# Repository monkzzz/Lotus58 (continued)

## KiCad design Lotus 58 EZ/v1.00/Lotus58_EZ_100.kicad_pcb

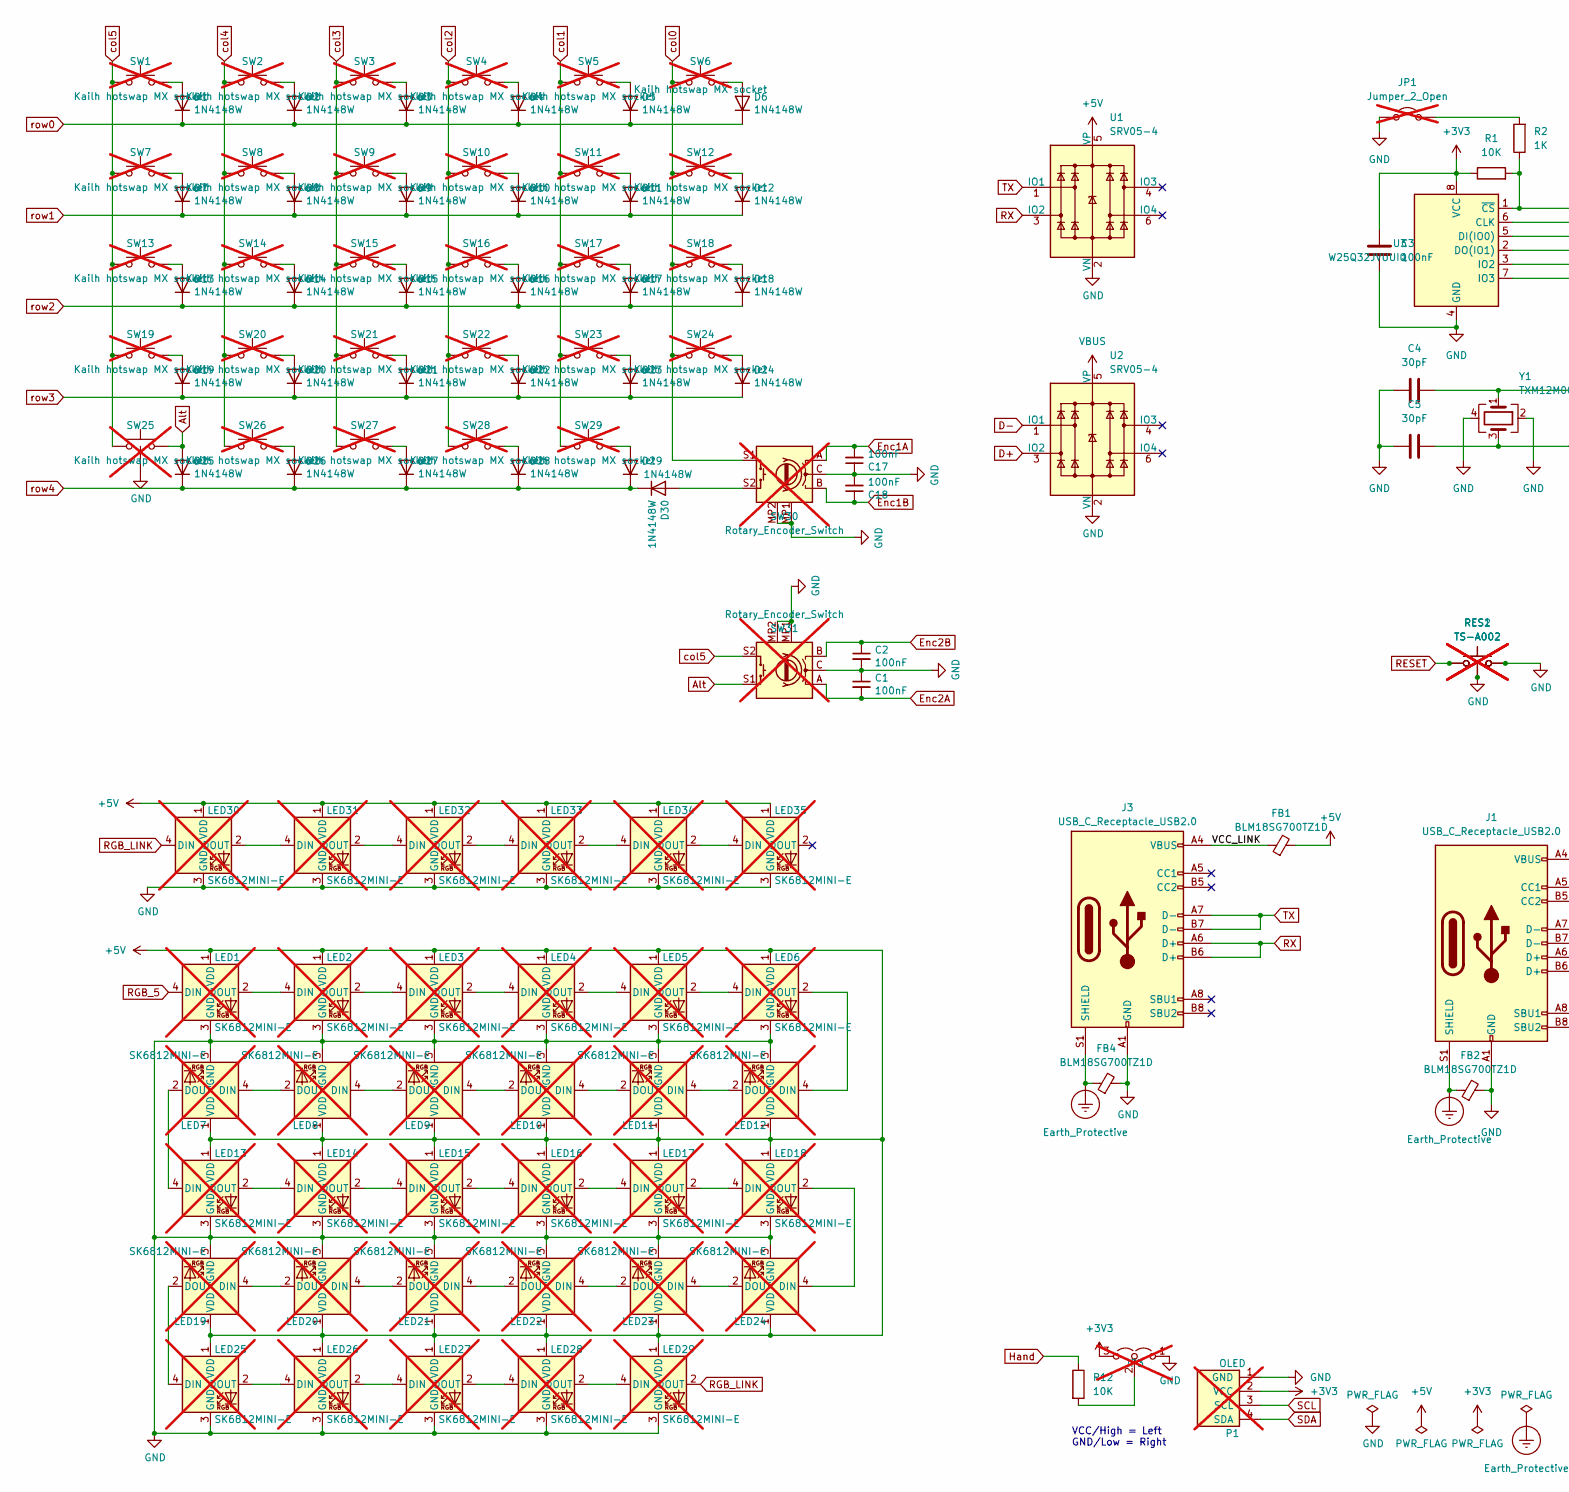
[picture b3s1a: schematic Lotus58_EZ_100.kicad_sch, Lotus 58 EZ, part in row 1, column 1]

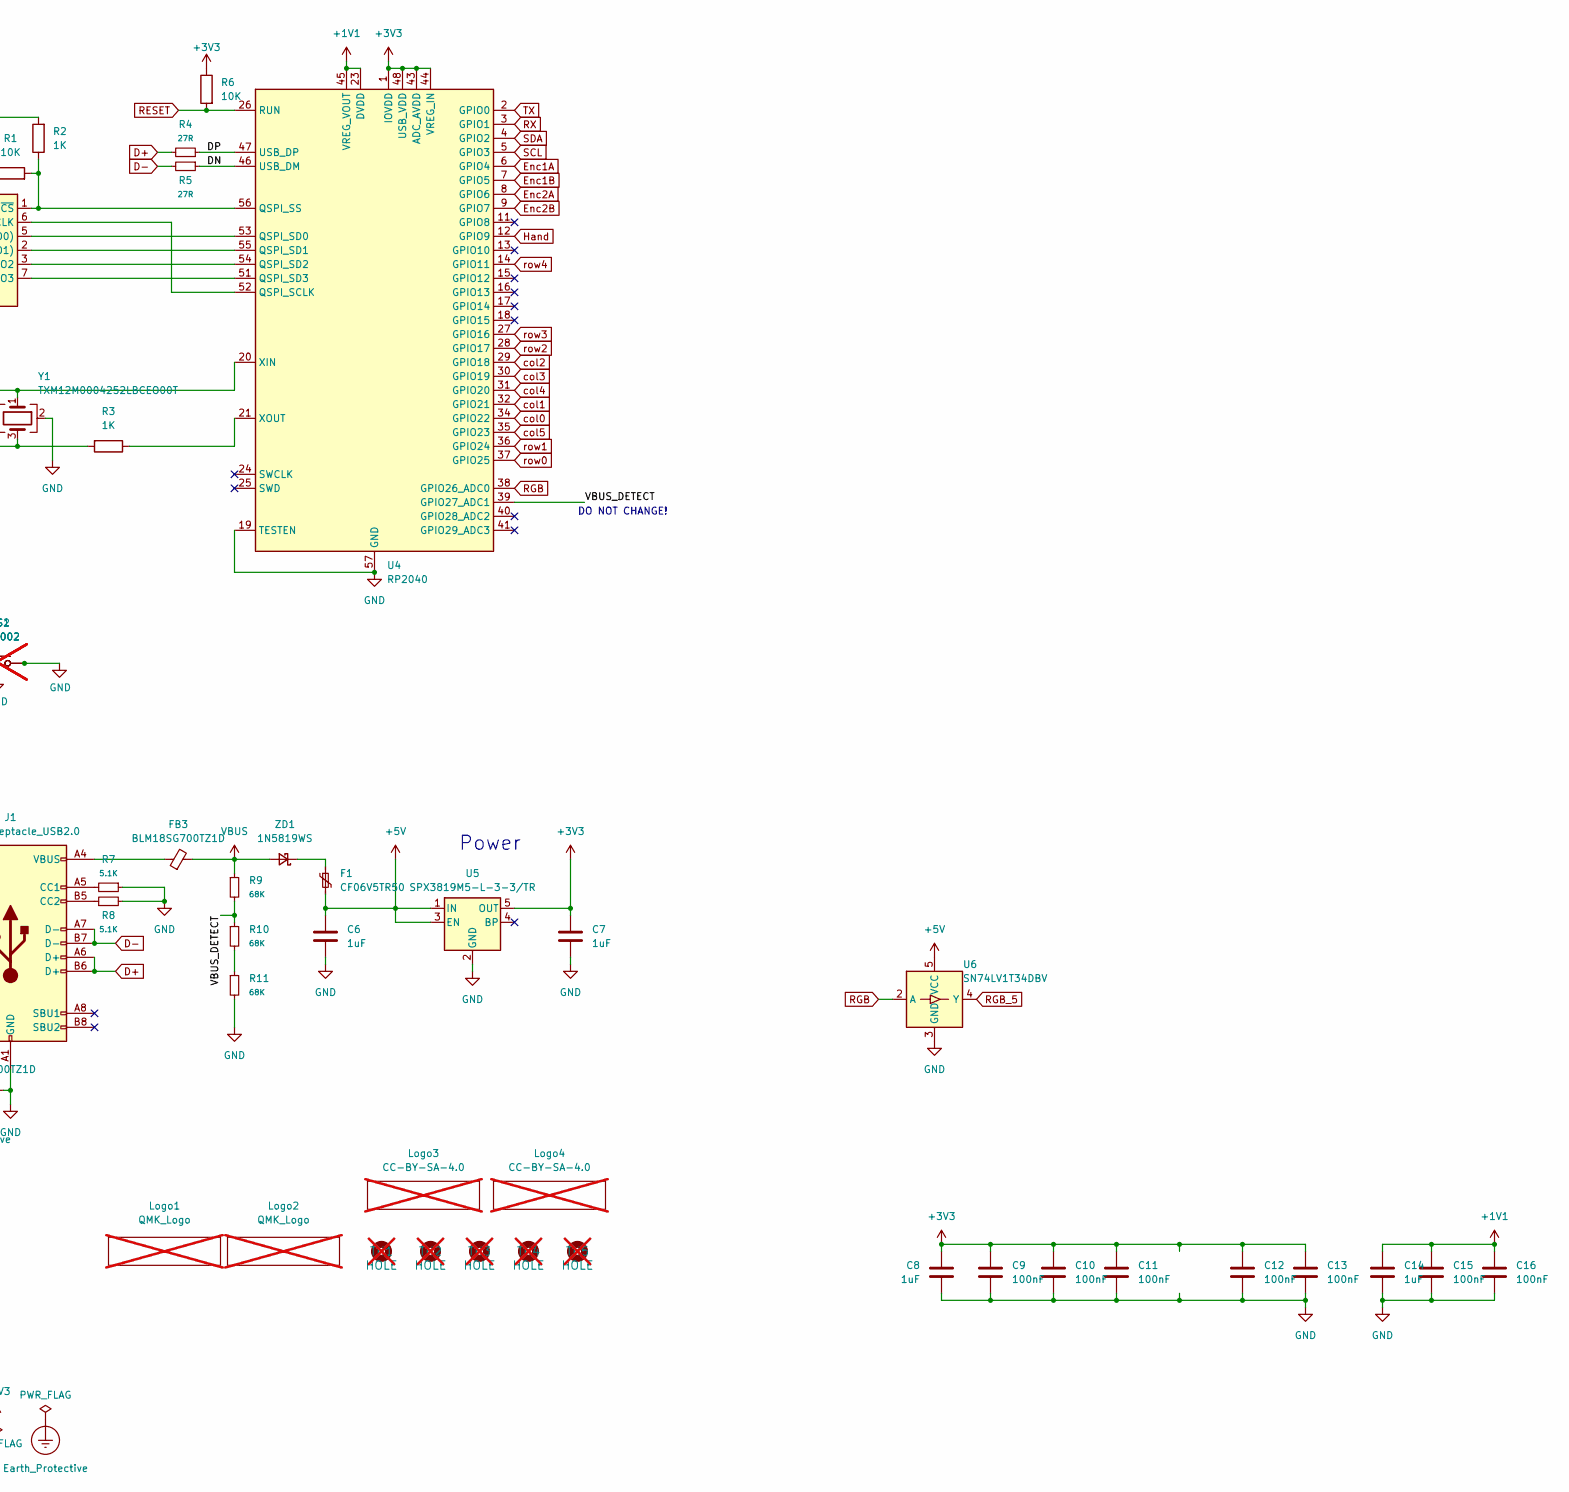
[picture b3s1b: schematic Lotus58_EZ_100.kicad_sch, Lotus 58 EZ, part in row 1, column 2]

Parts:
C1, C2, C3, C9, C10, C11, C12, C13, C15, C16, C17, C18: 100nF; C_0402_1005Metric; LCSC C1525
C4, C5: 30pF; C_0402_1005Metric; LCSC C1570
C6, C7, C8, C14: 1uF; C_0402_1005Metric; LCSC C52923
D1, D2, D3, D4, D5, D6, D7, D8, D9, D10, D11, D12, D13, D14, D15, D16, D17, D18, D19, D20, D21, D22, D23, D24, D25, D26, D27, D28, D29, D30: 1N4148W; Nexperia_CFP3_SOD-123W; LCSC C81598
F1: CF06V5TR50; R_0603_1608Metric; LCSC C163116
FB1, FB2, FB3, FB4: BLM18SG700TZ1D; C_0603_1608Metric_Pad1.08x0.95mm_HandSolder; LCSC C1002
J1, J3: USB_C_Receptacle_USB2.0; Molex-216990_GCT-USB45xx_HRO-TYPE-C-31-M-13x-PiMicro; LCSC C963373
JP1: Jumper_2_Open; Jumper_Mini; not fitted
JP3: LEFT; SolderJumper-3_P2.0mm_Open_TrianglePad1.0x1.5mm_NumberLabels; not fitted
LED1, LED2, LED3, LED4, LED5, LED6, LED7, LED8, LED9, LED10, LED11, LED12, LED13, LED14, LED15, LED16, LED17, LED18, LED19, LED20, LED21, LED22, LED23, LED24, LED25, LED26, LED27, LED28, LED29: SK6812MINI-E; MX_SK6812MINI-E_REVERSIBLE; not fitted
LED30, LED31, LED32, LED33, LED34, LED35: SK6812MINI-E; MX_SK6812MINI-E_REVERSIBLE_special_v2; not fitted
Logo1, Logo2: QMK_Logo; qmk logo; not fitted
Logo3, Logo4: CC-BY-SA-4.0; CC_BY_SA_40; not fitted
P1: OLED; SSD1306-0.91-OLED-4pin-128x32 doublesided; not fitted
R1, R6, R12: 10K; R_0402_1005Metric; LCSC C25744
R2, R3: 1K; R_0402_1005Metric; LCSC C11702
R4, R5: 27R; R_0402_1005Metric; LCSC C100353
R7, R8: 5.1K; R_0402_1005Metric; LCSC C25905
R9, R10, R11: 68K; R_0402_1005Metric; LCSC C137947
RES1, RES2: TS-A002; YTS-A002; LCSC C2888934; not fitted
SW1, SW2, SW3, SW4, SW5, SW6, SW7, SW8, SW9, SW10, SW11, SW12, SW13, SW14, SW15, SW16, SW17, SW18, SW19, SW20, SW21, SW22, SW23, SW24, SW26, SW27, SW28, SW29: Kailh hotswap MX socket; SW_MX_HotSwap_Reversible; not fitted
SW25: Kailh hotswap MX socket; SW_MX_HotSwap_Reversible_FOR encoder; not fitted
SW30, SW31: Rotary_Encoder_Switch; Encoder_Alps_EC11E_Small; not fitted
TH1, TH2, TH3, TH4, TH5: HOLE; Spacer PCB hole; not fitted
U1, U2: SRV05-4; SOT-23-6; LCSC C7420376
U3: W25Q32JVUUIQ; USON-8_4x3mm_P0.8mm; LCSC C2999380
U4: RP2040; QFN-56-1EP_7x7mm_P0.4mm_EP3.2x3.2mm; LCSC C2040
U5: SPX3819M5-L-3-3/TR; SOT-23-5; LCSC C9055
U6: SN74LV1T34DBV; SOT-23-5; LCSC C100024
Y1: TXM12M0004252LBCEO00T; Crystal_SMD_2520-4Pin_2.5x2.0mm; LCSC C284156
ZD1: 1N5819WS; D_SOD-323F; LCSC C191023

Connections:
+1V1: C14.1, C15.1, C16.1, U4.23 (DVDD), U4.45 (VREG_VOUT), U4.50 (DVDD)
+3V3: C3.1, C7.1, C8.1, C9.1, C10.1, C11.1, C12.1, C13.1, JP3.3 (B), P1.2 (VCC), R1.1, R6.1, U3.8 (VCC), U4.1 (IOVDD), U4.10 (IOVDD), U4.22 (IOVDD), U4.33 (IOVDD), U4.42 (IOVDD), U4.43 (ADC_AVDD), U4.44 (VREG_IN), U4.48 (USB_VDD), U4.49 (IOVDD), U5.5 (OUT)
+5V: C6.1, F1.2, FB1.2, LED1.1 (VDD), LED2.1 (VDD), LED3.1 (VDD), LED4.1 (VDD), LED5.1 (VDD), LED6.1 (VDD), LED7.1 (VDD), LED8.1 (VDD), LED9.1 (VDD), LED10.1 (VDD), LED11.1 (VDD), LED12.1 (VDD), LED13.1 (VDD), LED14.1 (VDD), LED15.1 (VDD), LED16.1 (VDD), LED17.1 (VDD), LED18.1 (VDD), LED19.1 (VDD), LED20.1 (VDD), LED21.1 (VDD), LED22.1 (VDD), LED23.1 (VDD), LED24.1 (VDD), LED25.1 (VDD), LED26.1 (VDD), LED27.1 (VDD), LED28.1 (VDD), LED29.1 (VDD), LED30.1 (VDD), LED31.1 (VDD), LED32.1 (VDD), LED33.1 (VDD), LED34.1 (VDD), LED35.1 (VDD), U1.5 (VP), U5.1 (IN), U5.3 (EN), U6.5 (VCC)
/DN: R5.1, U4.46 (USB_DM)
/DP: R4.1, U4.47 (USB_DP)
/VBUS_DETECT: R9.2, R10.1, U4.39 (GPIO27_ADC1)
/VCC_LINK: FB1.1, J3.A4 (VBUS), J3.A9 (VBUS), J3.B4 (VBUS), J3.B9 (VBUS)
Alt: D25.2 (A), SW25.2, SW31.S1
D+: J1.A6 (D+), J1.B6 (D+), R4.2, U2.3 (IO2)
D-: J1.A7 (D-), J1.B7 (D-), R5.2, U2.1 (IO1)
Earth_Protective: FB2.1, FB4.1, J1.S1 (SHIELD), J3.S1 (SHIELD)
Enc1A: C17.2, SW30.A, U4.6 (GPIO4)
Enc1B: C18.1, SW30.B, U4.7 (GPIO5)
Enc2A: C1.2, SW31.A, U4.8 (GPIO6)
Enc2B: C2.1, SW31.B, U4.9 (GPIO7)
GND: C1.1, C2.2, C3.2, C4.2, C5.2, C6.2, C7.2, C8.2, C9.2, C10.2, C11.2, C12.2, C13.2, C14.2, C15.2, C16.2, C17.1, C18.2, FB2.2, FB4.2, J1.A1 (GND), J1.A12 (GND), J1.B1 (GND), J1.B12 (GND), J3.A1 (GND), J3.A12 (GND), J3.B1 (GND), J3.B12 (GND), JP1.1 (A), JP3.1 (A), LED1.3 (GND), LED2.3 (GND), LED3.3 (GND), LED4.3 (GND), LED5.3 (GND), LED6.3 (GND), LED7.3 (GND), LED8.3 (GND), LED9.3 (GND), LED10.3 (GND), LED11.3 (GND), LED12.3 (GND), LED13.3 (GND), LED14.3 (GND), LED15.3 (GND), LED16.3 (GND), LED17.3 (GND), LED18.3 (GND), LED19.3 (GND), LED20.3 (GND), LED21.3 (GND), LED22.3 (GND), LED23.3 (GND), LED24.3 (GND), LED25.3 (GND), LED26.3 (GND), LED27.3 (GND), LED28.3 (GND), LED29.3 (GND), LED30.3 (GND), LED31.3 (GND), LED32.3 (GND), LED33.3 (GND), LED34.3 (GND), LED35.3 (GND), P1.1 (GND), R7.1, R8.2, R11.2, RES1.2, RES1.3, RES2.1, RES2.3, SW25.3, SW30.C, SW30.MP1 (GND), SW30.MP2 (GND), SW31.C, SW31.MP1 (GND), SW31.MP2 (GND), U1.2 (VN), U2.2 (VN), U3.4 (GND), U4.19 (TESTEN), U4.57 (GND), U5.2 (GND), U6.3 (GND), Y1.2, Y1.4
Hand: R12.1, U4.12 (GPIO9)
unnamed: C5.1, R3.2, Y1.3
unnamed: D1.2 (A), SW1.1
unnamed: D2.2 (A), SW2.1
unnamed: D3.2 (A), SW3.1
unnamed: D4.2 (A), SW4.1
unnamed: D5.2 (A), SW5.1
unnamed: D6.2 (A), SW6.1
unnamed: D7.2 (A), SW7.1
unnamed: D8.2 (A), SW8.1
unnamed: D9.2 (A), SW9.1
unnamed: D10.2 (A), SW10.1
unnamed: D11.2 (A), SW11.1
unnamed: D12.2 (A), SW12.1
unnamed: D13.2 (A), SW13.1
unnamed: D14.2 (A), SW14.1
unnamed: D15.2 (A), SW15.1
unnamed: D16.2 (A), SW16.1
unnamed: D17.2 (A), SW17.1
unnamed: D18.2 (A), SW18.1
unnamed: D19.2 (A), SW19.1
unnamed: D20.2 (A), SW20.1
unnamed: D21.2 (A), SW21.1
unnamed: D22.2 (A), SW22.1
unnamed: D23.2 (A), SW23.1
unnamed: D24.2 (A), SW24.1
unnamed: D26.2 (A), SW26.1
unnamed: D27.2 (A), SW27.1
unnamed: D28.2 (A), SW28.1
unnamed: D29.2 (A), SW29.1
unnamed: D30.2 (A), SW30.S2
unnamed: FB3.1, J1.A4 (VBUS), J1.A9 (VBUS), J1.B4 (VBUS), J1.B9 (VBUS)
unnamed: J1.A5 (CC1), R7.2
unnamed: J1.B5 (CC2), R8.1
unnamed: JP1.2 (B), R2.2
unnamed: JP3.2 (C), R12.2
unnamed: LED1.2 (DOUT), LED2.4 (DIN)
unnamed: LED2.2 (DOUT), LED3.4 (DIN)
unnamed: LED3.2 (DOUT), LED4.4 (DIN)
unnamed: LED4.2 (DOUT), LED5.4 (DIN)
unnamed: LED5.2 (DOUT), LED6.4 (DIN)
unnamed: LED7.4 (DIN), LED8.2 (DOUT)
unnamed: LED8.4 (DIN), LED9.2 (DOUT)
unnamed: LED10.4 (DIN), LED11.2 (DOUT)
unnamed: LED9.4 (DIN), LED10.2 (DOUT)
unnamed: LED11.4 (DIN), LED12.2 (DOUT)
unnamed: LED6.2 (DOUT), LED12.4 (DIN)
unnamed: LED7.2 (DOUT), LED13.4 (DIN)
unnamed: LED13.2 (DOUT), LED14.4 (DIN)
unnamed: LED14.2 (DOUT), LED15.4 (DIN)
unnamed: LED15.2 (DOUT), LED16.4 (DIN)
unnamed: LED16.2 (DOUT), LED17.4 (DIN)
unnamed: LED17.2 (DOUT), LED18.4 (DIN)
unnamed: LED18.2 (DOUT), LED24.4 (DIN)
unnamed: LED19.4 (DIN), LED20.2 (DOUT)
unnamed: LED19.2 (DOUT), LED25.4 (DIN)
unnamed: LED20.4 (DIN), LED21.2 (DOUT)
unnamed: LED21.4 (DIN), LED22.2 (DOUT)
unnamed: LED22.4 (DIN), LED23.2 (DOUT)
unnamed: LED23.4 (DIN), LED24.2 (DOUT)
unnamed: LED25.2 (DOUT), LED26.4 (DIN)
unnamed: LED26.2 (DOUT), LED27.4 (DIN)
unnamed: LED27.2 (DOUT), LED28.4 (DIN)
unnamed: LED28.2 (DOUT), LED29.4 (DIN)
unnamed: LED30.2 (DOUT), LED31.4 (DIN)
unnamed: LED31.2 (DOUT), LED32.4 (DIN)
unnamed: LED32.2 (DOUT), LED33.4 (DIN)
unnamed: LED33.2 (DOUT), LED34.4 (DIN)
unnamed: LED34.2 (DOUT), LED35.4 (DIN)
unnamed: R10.2, R11.1
unnamed: U3.6 (CLK), U4.52 (QSPI_SCLK)
unnamed: U3.5 (DI(IO0)), U4.53 (QSPI_SD0)
unnamed: U3.2 (DO(IO1)), U4.55 (QSPI_SD1)
unnamed: U3.3 (IO2), U4.54 (QSPI_SD2)
unnamed: U3.7 (IO3), U4.51 (QSPI_SD3)
unnamed: R1.2, R2.1, U3.1 (~CS), U4.56 (QSPI_SS)
unnamed: C4.1, U4.20 (XIN), Y1.1
unnamed: R3.1, U4.21 (XOUT)
unnamed: F1.1, ZD1.1 (K)
RESET: R6.2, RES1.1, RES2.2, U4.26 (RUN)
RGB: U4.38 (GPIO26_ADC0), U6.2 (A)
RGB_5: LED1.4 (DIN), U6.4 (Y)
RGB_LINK: LED29.2 (DOUT), LED30.4 (DIN)
RX: J3.A6 (D+), J3.B6 (D+), U1.3 (IO2), U4.3 (GPIO1)
SCL: P1.3 (SCL), U4.5 (GPIO3)
SDA: P1.4 (SDA), U4.4 (GPIO2)
TX: J3.A7 (D-), J3.B7 (D-), U1.1 (IO1), U4.2 (GPIO0)
VBUS: FB3.2, R9.1, U2.5 (VP), ZD1.2 (A)
col0: SW6.2, SW12.2, SW18.2, SW24.2, SW30.S1, U4.34 (GPIO22)
col1: SW5.2, SW11.2, SW17.2, SW23.2, SW29.2, U4.32 (GPIO21)
col2: SW4.2, SW10.2, SW16.2, SW22.2, SW28.2, U4.29 (GPIO18)
col3: SW3.2, SW9.2, SW15.2, SW21.2, SW27.2, U4.30 (GPIO19)
col4: SW2.2, SW8.2, SW14.2, SW20.2, SW26.2, U4.31 (GPIO20)
col5: SW1.2, SW7.2, SW13.2, SW19.2, SW25.1, SW31.S2, U4.35 (GPIO23)
row0: D1.1 (K), D2.1 (K), D3.1 (K), D4.1 (K), D5.1 (K), D6.1 (K), U4.37 (GPIO25)
row1: D7.1 (K), D8.1 (K), D9.1 (K), D10.1 (K), D11.1 (K), D12.1 (K), U4.36 (GPIO24)
row2: D13.1 (K), D14.1 (K), D15.1 (K), D16.1 (K), D17.1 (K), D18.1 (K), U4.28 (GPIO17)
row3: D19.1 (K), D20.1 (K), D21.1 (K), D22.1 (K), D23.1 (K), D24.1 (K), U4.27 (GPIO16)
row4: D25.1 (K), D26.1 (K), D27.1 (K), D28.1 (K), D29.1 (K), D30.1 (K), U4.14 (GPIO11)

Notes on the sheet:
Power
VCC/High = Left GND/Low = Right
DO NOT CHANGE!

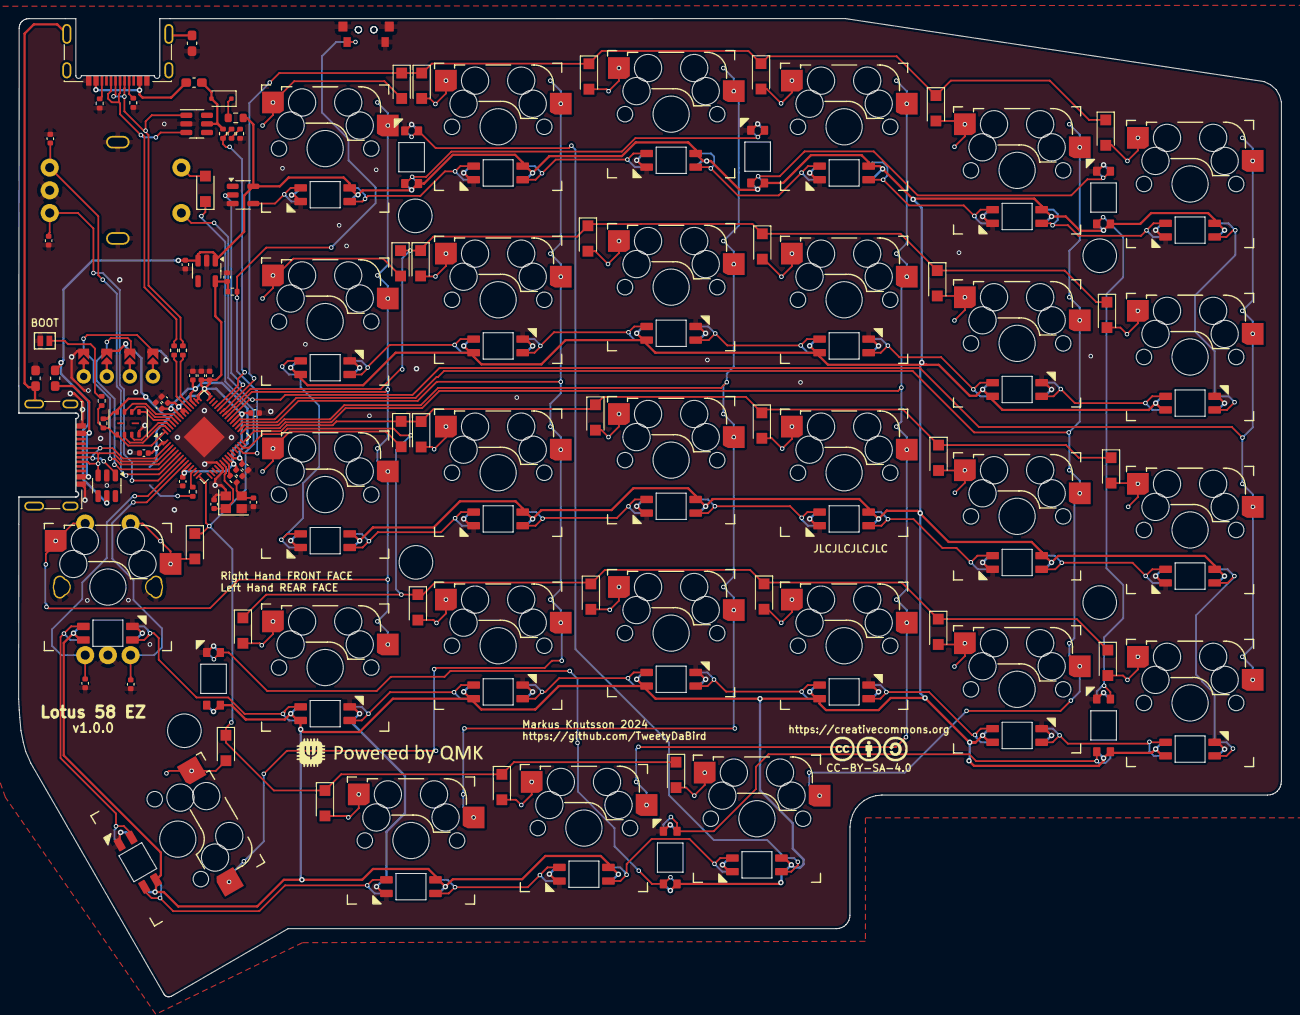
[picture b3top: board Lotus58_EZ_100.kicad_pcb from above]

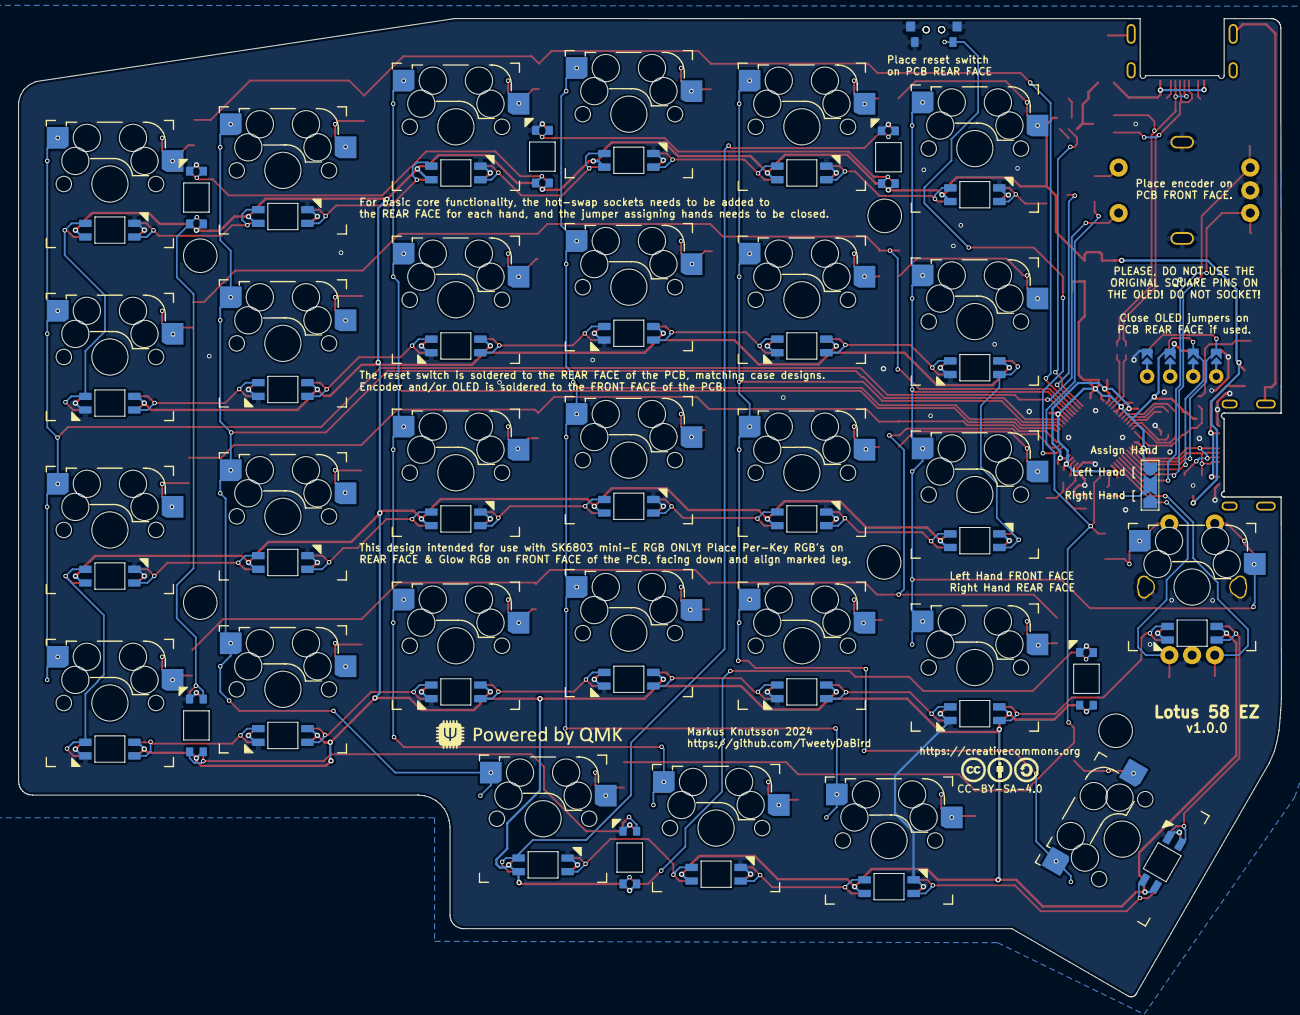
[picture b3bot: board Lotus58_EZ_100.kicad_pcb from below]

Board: 2 copper layers, 139.1 x 107.7 mm, 155 parts (4 on the bottom side), 115 nets.

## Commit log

2023-11-22 Housekeeping
2023-12-27 Initial commit v1.28
2024-01-11 Move files
2024-01-11 House cleaning
2024-01-11 v1.41
    Changed silkscreeen
2024-01-11 Tweaked 1.41
2024-03-28 v1.29
2024-04-07 Renamed folders
    Making place for new versions, housekeeping of files
2024-04-14 USB-C v1.42
    mirror to allow PCBA
2024-05-16 Lotus 58 Classic
    Intial design v1.00
2024-05-19 Lotus 58 Classic
    Tweaks
2024-05-19 Lotus 58 EZ
    Tweaks
2024-09-19 Inconsistent files
2025-02-07 Add - PDF versions of schematics 1.24 / 1.28 / 1.30
2025-04-03 Lotus 58 - USB Link v1.50
2025-04-03 Lotus 58 - Plate
    added nice!view
2025-04-03 Lotus 58 - USB Link v1.51
    adjusted RGB Gl
    ow, Silkscreen
2025-04-03 Lotus 58 - TRRS Link v1.30
2025-04-03 test bom
2025-04-03 Revert "test bom"
    This reverts commit 6c63932caec8bfd1a810df5035c629821b470d4d.
2025-04-03 Corrected iBom
2025-04-03 Corrected iBom
    USB v1.51
2025-04-03 Lotus 58 - TRRS Link v1.30
    release ready
